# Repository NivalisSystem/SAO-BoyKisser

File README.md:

# SAO-BoyKisser
SAO BoyKisser

Created with gremlin energy, provided as is, enjoy! (Or don't!)

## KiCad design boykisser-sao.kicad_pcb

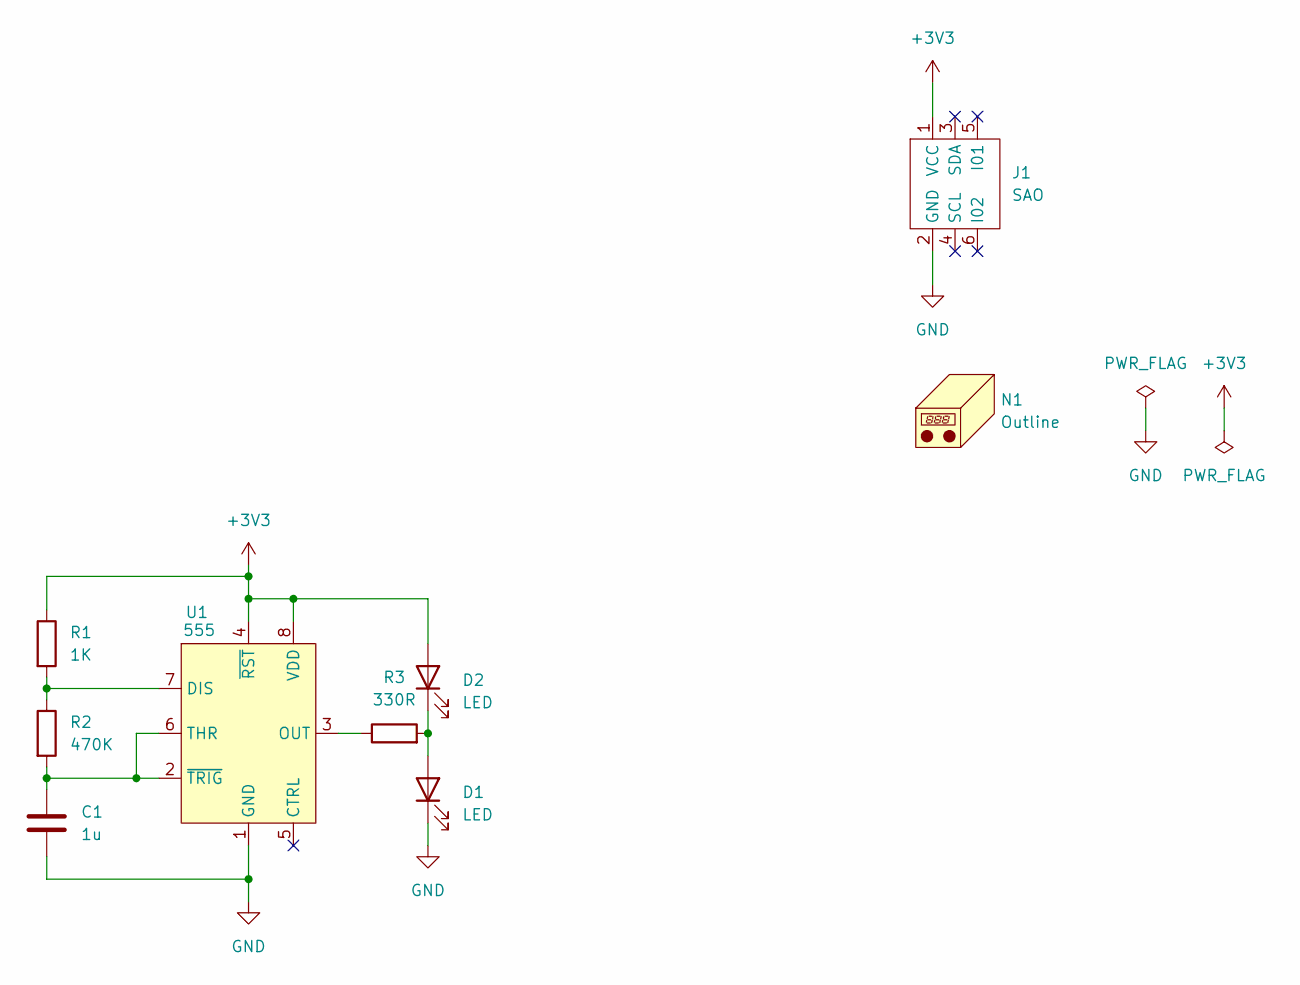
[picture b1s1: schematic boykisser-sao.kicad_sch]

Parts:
C1: 1u; C_1206_3216Metric_Pad1.33x1.80mm_HandSolder
D1, D2: LED; LED_D5.0mm
J1: SAO; IDC-Header_2x03_P2.54mm_Vertical
N1: Outline; Boy-Kisser
R1: 1K; R_1206_3216Metric_Pad1.30x1.75mm_HandSolder
R2: 470K; R_1206_3216Metric_Pad1.30x1.75mm_HandSolder
R3: 330R; R_1206_3216Metric_Pad1.30x1.75mm_HandSolder
U1: 555; SOIC-8_3.9x4.9mm_P1.27mm

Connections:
+3V3: D2.2 (A), J1.1 (VCC), R1.1, U1.4 (~RST), U1.8 (VDD)
GND: C1.2, D1.1 (K), J1.2 (GND), U1.1 (GND)
unnamed: D1.2 (A), D2.1 (K), R3.2
unnamed: R1.2, R2.1, U1.7 (DIS)
unnamed: R3.1, U1.3 (OUT)
unnamed: C1.1, R2.2, U1.2 (~TRIG), U1.6 (THR)

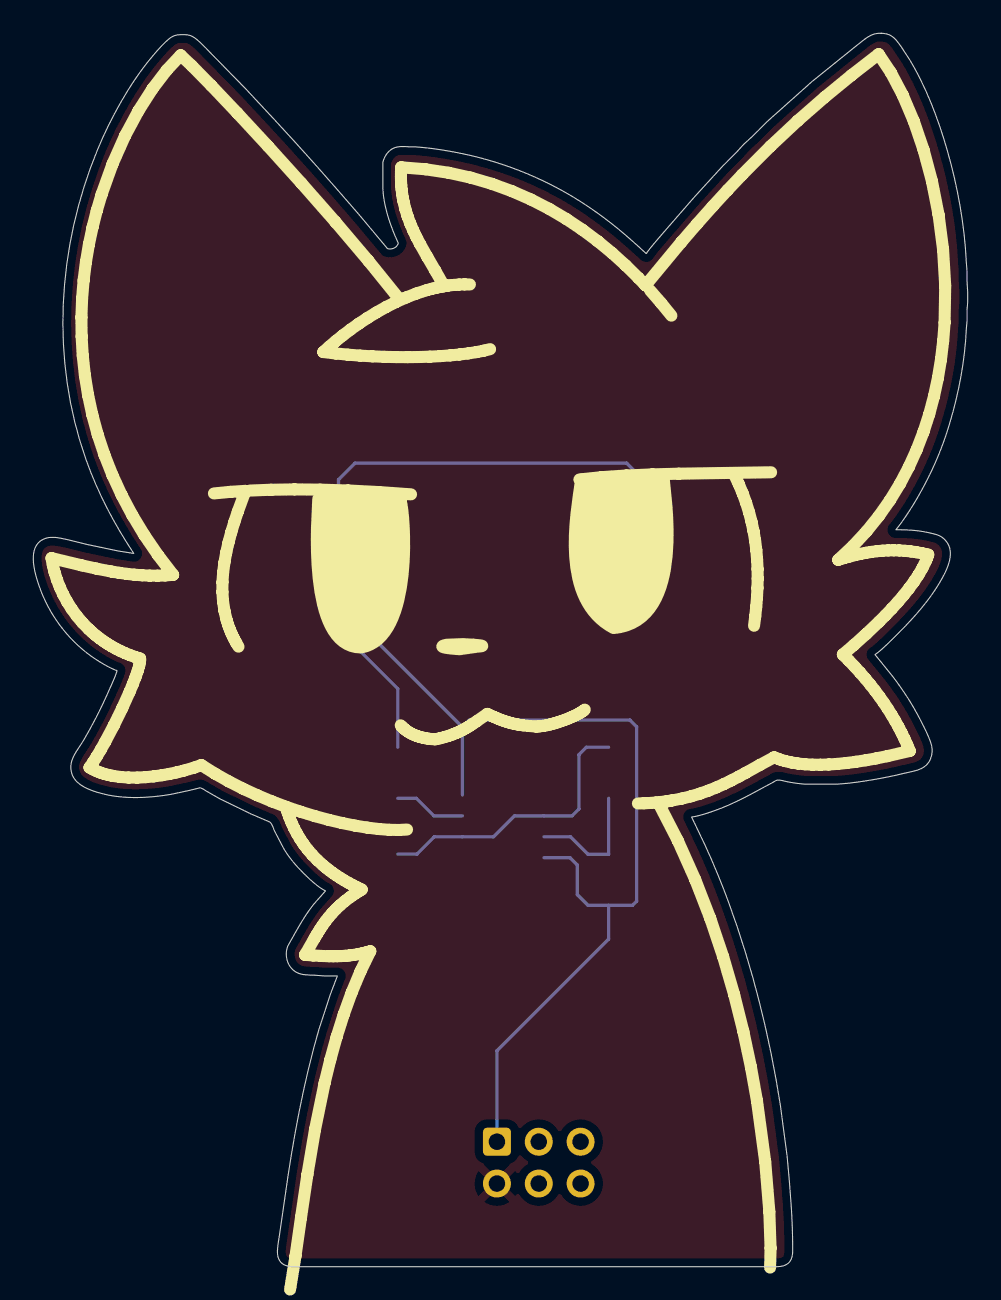
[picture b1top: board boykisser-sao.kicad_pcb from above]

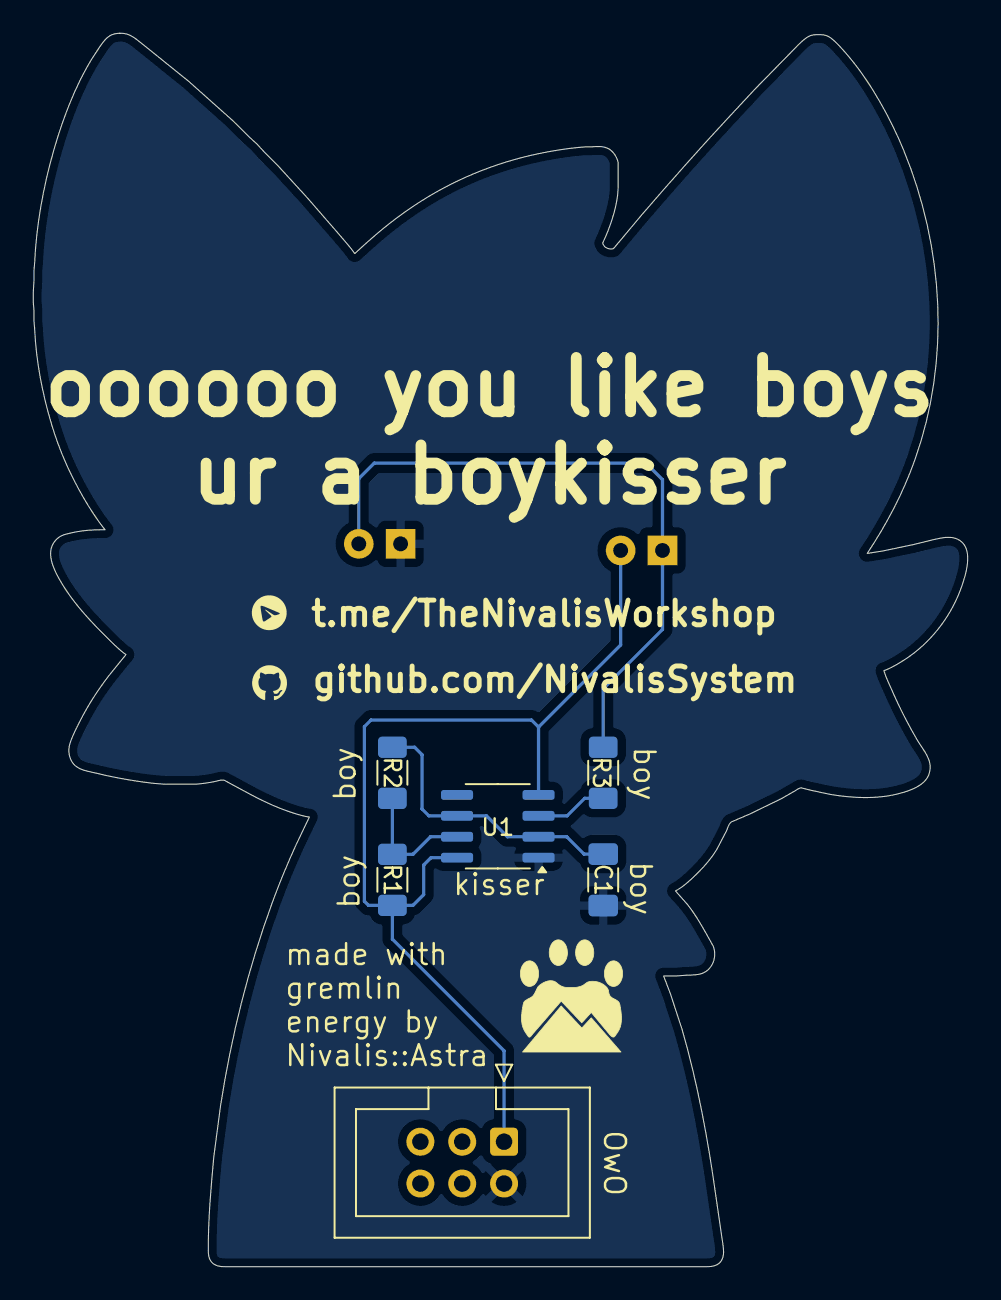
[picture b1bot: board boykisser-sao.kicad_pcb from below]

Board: 2 copper layers, 56.7 x 74.9 mm, 9 parts (6 on the bottom side), 6 nets.

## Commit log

2024-09-07 Create LICENSE
2024-09-07 Initial commit
    Provided as is, likely to never be updated again! Enjoy!
2024-09-07 add image!
